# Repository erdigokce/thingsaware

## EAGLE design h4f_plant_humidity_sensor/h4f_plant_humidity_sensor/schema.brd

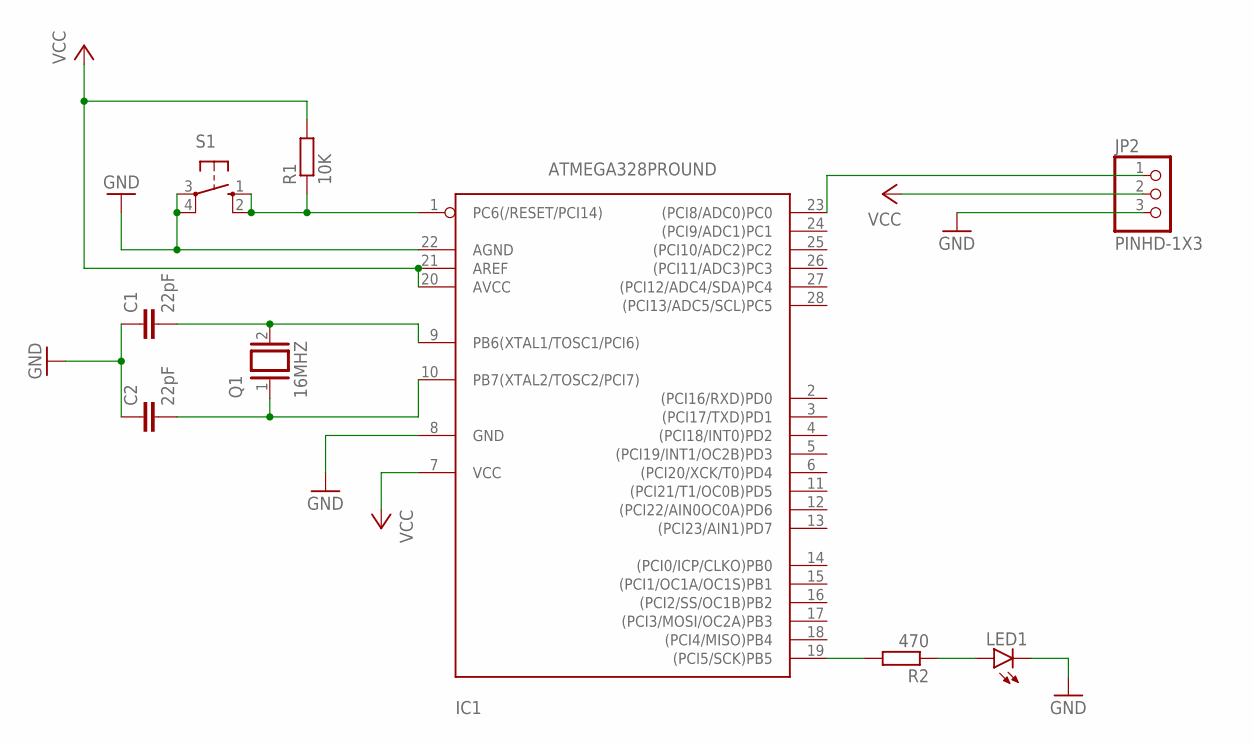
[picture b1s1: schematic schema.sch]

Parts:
C1, C2: 22pF; C025-025X050
IC1: ATMEGA328PROUND; DIL28-3-ROUND
JP2: PINHD-1X3; 1X03
LED1: LED3MM
Q1: 16MHZ; QS
R1: 10K; 0204/7
R2: 470; 0204/7
S1: 10-XX; B3F-10XX

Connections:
GND: C1.1, C2.1, IC1.8 (GND), IC1.22 (AGND), JP2.3, LED1.K (C), S1.3, S1.4 (P1)
unnamed: IC1.19 ((PCI5/SCK)PB5), R2.2
unnamed: IC1.1 (PC6(/RESET/PCI14)), R1.1, S1.1 (S), S1.2 (S1)
unnamed: C2.2, IC1.10 (PB7(XTAL2/TOSC2/PCI7)), Q1.1
unnamed: LED1.A, R2.1
unnamed: C1.2, IC1.9 (PB6(XTAL1/TOSC1/PCI6)), Q1.2
unnamed: IC1.23 ((PCI8/ADC0)PC0), JP2.1
VCC: IC1.7 (VCC), IC1.20 (AVCC), IC1.21 (AREF), JP2.2, R1.2

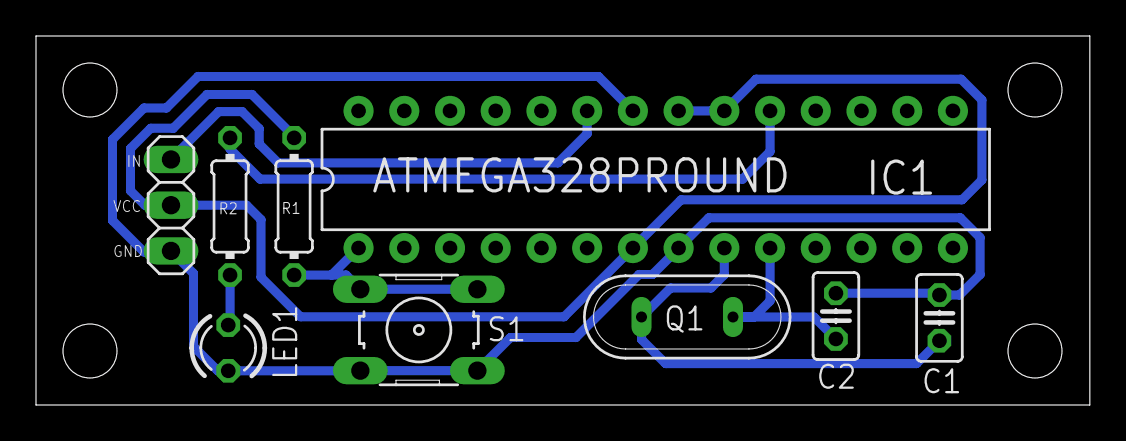
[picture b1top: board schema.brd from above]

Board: 2 copper layers, 58.5 x 20.5 mm, 9 parts (0 on the bottom side), 8 nets.

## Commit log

2020-02-27 Servo and sleep mode implementation.
2020-03-05 Schema of the product has been added. Functionality of pushing lever to down has been added. Timings arranged.
2020-03-05 LICENSE added. ReadMe updated.
2020-03-14 Updates after rearranging servo position on the flusher.
2020-04-21 ReadMe.adoc and R2 resistor updated due to LDR selection has been changed.
2020-04-21 Typos and misinformation fix.
2020-10-07 Schema edited.
2020-11-04 Plant humidity sensor initial commit.
2020-11-09 Schematics and code revision.
2020-11-10 Box design added.
2022-09-06 Thingsaware migration
2022-09-07 AP mode WiFi setting recieve fix. EEPROM router save fix. STA server initialization fix.
2022-09-07 mDNS add service
2022-09-08 platform io migration
2022-09-10 Motor control and remaining info implementations
2022-09-13 modular structure
2022-09-13 designs
2022-10-16 pet feeder system design
2022-10-16 service talks with mqtt broker
2022-10-21 change direction of schedule-feed topic
2022-10-30 initial services
2022-10-30 gitignore
2022-10-31 services init
2022-10-31 service discovery with consul developments
2022-11-04 service registration and de-registration to consul
2022-11-06 Added thingsaware_services_arc.drawio
2022-11-11 service de-registration fix with TCP healthchecks.
2023-01-22 renaming space service
2023-01-30 user service kafka developments
2023-02-03 user service postgresql initialization
2023-02-22 Apicurio registry and avro generation integration
2023-08-03 user service rest nature and repository pattern
2023-08-04 user service initial implementation
